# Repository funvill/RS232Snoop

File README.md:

# RS232Snoop

A simple PCB with diodes to allow for RS232 snooping. Made in [KiCad](https://docs.kicad.org/)

[PCB preview](https://kicanvas.org/?github=https://github.com/funvill/RS232Snoop/tree/main/hardware) via KiCanvas

## Parts list

- [1N4148WS](https://www.digikey.com/en/products/detail/onsemi/1N4148WS/1873805?msockid=20aab5989895639f2f81a754992c6286) - Diodes
- [PhoenixContact 1x03 P3.81mm Horizontal](https://www.digikey.com/en/products/detail/phoenix-contact/1803280/260575) - Screw terminals

## Preview

### Front

### Back

### Schematic

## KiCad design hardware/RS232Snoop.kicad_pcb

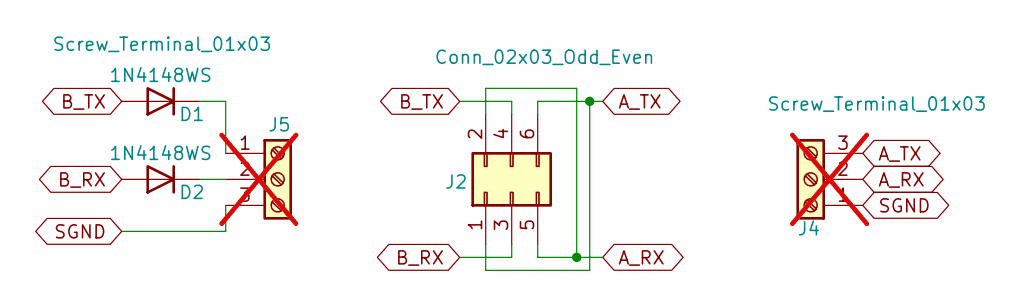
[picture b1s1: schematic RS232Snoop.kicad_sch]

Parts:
D1, D2: 1N4148WS; D_SOD-323; JLCPCB Part # C2128
J2: Conn_02x03_Odd_Even; PinHeader_2x03_P2.54mm_Vertical
J4, J5: Screw_Terminal_01x03; PhoenixContact_MC_1,5_3-G-3.81_1x03_P3.81mm_Horizontal; not fitted

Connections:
A_RX: J2.2, J2.5, J4.2
A_TX: J2.1, J2.6, J4.3
B_RX: D2.2 (A), J2.3
B_TX: D1.2 (A), J2.4
unnamed: D1.1 (K), J5.1
unnamed: D2.1 (K), J5.2
SGND: J4.1, J5.3

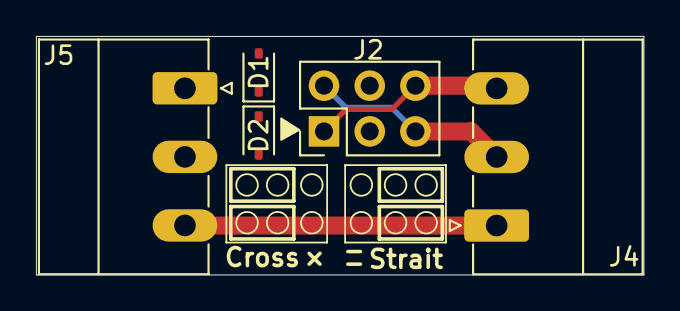
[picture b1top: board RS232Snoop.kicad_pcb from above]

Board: 2 copper layers, 33.8 x 13.2 mm, 5 parts (0 on the bottom side), 7 nets.

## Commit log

2025-04-01 Added initials design
2025-04-02 Added headers for straight or crossover
